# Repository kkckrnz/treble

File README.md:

# Treble
Treble keyboard is a 42 key, low profile choc v1, monoblock, moderate column staggered, wireless/wired mechanical keyboard powered by pro micro compatible MCU board. It is designed with [ergogen](https://github.com/ergogen/ergogen), the ergonomic keyboard generator.

The sandwich PCB design concept came from [Horizon keyboard](https://github.com/skarrmann/horizon). Bottom plate cutouts for through-hole pins makes it so that keyboard can be put on any surface, and the cover plate hides all the other internal components. Overall, this design makes the keyboard clean, low profile and look more finished without needing a dedicated case.

## Features
- Rectangular design for improved stability; easier to place on your lap or a laptop
- Low profile: total height is about 15mm tall
- Compact: overall size smaller than Apple Magic Keyboard
- Column staggered: mildly staggered so it's easy transition from row staggered keyboard yet it provides more comfortable typing experience
- 6 thumb keys: enough thumb keys for switching to different layers
- PCBs-for-case design
- Wireless/Wired depending on your preference

## Bill of Materials

| **Part**                             | **Quantity** | **Notes**                                           |
| ------------------------------------ | ------------ | --------------------------------------------------- |
| **Main PCB**                         | 1            | treble_vx.x.zip                                     |
| **Cover plate PCB**                  | 1            | treble_vx.x_cover_plate.zip                         |
| **Bottom plate PCB**                 | 1            | treble_vx.x_bottom_plate.zip                        |
| **MCU board**                        | 1            | Pro Micro compatible board                          |
| **Machine Sockets**                  | 2            | Mill-Max 310                                        |
| **Machine Socket Pins**              | 24           | Mill-Max 3320                                       |
| **Key switches**                     | 42           | Choc v1                                             |
| **Keycaps**                          | 42           | Choc v1 compatible                                  |
| **Diodes**                           | 42           | 1N4148 SOD-123                                      |
| **Reset switch**                     | 1            | EVQPU                                               |
| **Power switch**                     | 1            | MSK-12C02                                           |
| **JST connector (female)**           | 1            | S2B-PH-K-S                                          |
| **JST connector (male)**             | 1            |                                                     |
| **Battery**                          | 1            | 301230 110mAh 3.7V LiPo                             |
| **M2 6mm screws**                    | 12           |                                                     |
| **M2 nuts**                          | 4            |                                                     |
| **M2 8mm standoffs (female-female)** | 4            |                                                     |
| **Rubber feet**                      | 6            |                                                     |

- Male JST connector is only needed if the battery doesn't come with it
- You don't need Power switch, JST connector, and Battery if you build a wired keyboard

## Printable Treble
Download [Treble-A4.pdf](/docs/treble-A4.pdf) and print it (scale at 100%). Test the keyboard layout with your own hands.

## PCB order guide
1. Download gerber files from *Releases* on sidebar
2. Submit gerber files to PCB manufacturer
3. Select manufacturing options
4. Order

### JLCPCB manufacturing options
Most options are default. Changed options in *italic*:
- Base Material: FR-4
- Layers: 2
- Dimensions: (automatically filled in)
- PCB Qty: 5
- Product Type: Industrial/Consumer electronics
- Different Design: 1
- Delivery Format: Single PCB
- PCB Thickness: 1.6
- PCB Color: *Black*
- Silkscreen: White
- Surface Finish: *LeadFree HASL*
- Outer Copper Weight: 1 oz
- Via Covering: Tented
- Min via hole size/diameter: 0.3mm/(0.4/0.45mm)
- Board Outline Tolerance: ±0.2mm(Regular)
- Confirm Production file: No
- Mark on PCB: *Remove Mark*
- Electrical Test: Flying Probe Fully Test
- Gold Fingers: No
- Castellated Holes: No
- Edge Plating: No

I recommend **LeadFree HASL** option because you will be handling the keyboard directly without a case. Pick the PCB color of your choice. **Remove Mark** so you won't see random number printed on the PCB.

## Firmware
### ZMK
1. Setup GitHub Repo by following [ZMK documentation](https://zmk.dev/docs/user-setup#github-repo)
2. Setup User Config by following [ZMK documentation](https://zmk.dev/docs/user-setup#user-config-setup-script)	
3. Copy & Paste `/boards`, `/config`, and `build.yaml` from [zmk-config folder](/firmware/zmk-config) in this repo to zmk-config folder in your repo
4. Customise `treble.keymap` and `treble.conf` files in `/config` however you like it. Then push changes to your repo
```
git add .
git commit -m "commit message"
git push -u origin main
```
5. Install firmware by following [ZMK documentation](https://zmk.dev/docs/user-setup#installing-the-firmware)

- If you use MCU board other than nice!nano v2, then you will have to edit `build.yaml` file.
- [Precompiled firmware](/firmware/treble-nice_nano_v2-zmk.uf2.zip) is also available.
- There's [video guide](https://www.youtube.com/watch?v=O_urj-rF3bQ) by Joe Scotto if you would rather setup from scratch.

### Other Firmware
Since the keyboard is pro micro compatible it should be able to run QMK & KMK as well (not tested).

## Build guide
Follow [Build Guide](docs/treble_build_guide.md) to assemble the keyboard.

## Feedback
For any issues or questions please let me know.

If you have built and enjoyed the keyboard, consider supporting me.

Future development ideas:
- QMK & KMK firmware
- Hot swap switch support
- Low profile case
- MX version

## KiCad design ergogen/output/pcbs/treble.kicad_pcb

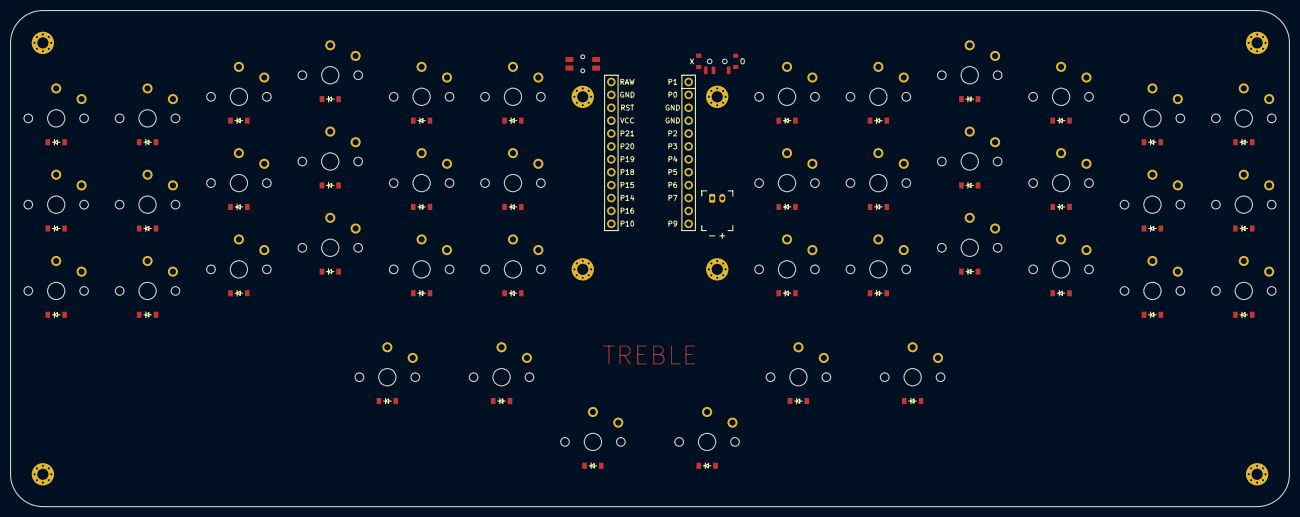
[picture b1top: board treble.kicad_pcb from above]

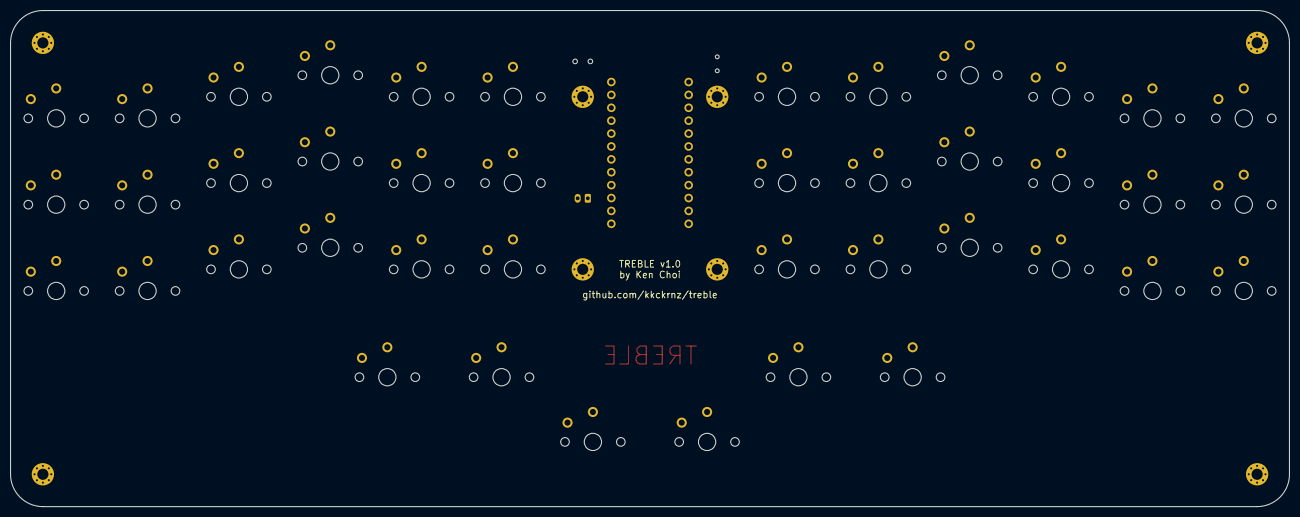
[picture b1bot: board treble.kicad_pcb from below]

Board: 2 copper layers, 252.0 x 97.8 mm, 141 parts (42 on the bottom side), 59 nets, no tracks yet.

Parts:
CJ1: CutoutMCU
CM1: CutoutMCU
CS1, CS2, CS3, CS4, CS5, CS6, CS7, CS8, CS9, CS10, CS11, CS12, CS13, CS14, CS15, CS16, CS17, CS18, CS19, CS20, CS21, CS22, CS23, CS24, CS25, CS26, CS27, CS28, CS29, CS30, CS31, CS32, CS33, CS34, CS35, CS36, CS37, CS38, CS39, CS40, CS41, CS42: CutoutSwitch
D1, D2, D3, D4, D5, D6, D7, D8, D9, D10, D11, D12, D13, D14, D15, D16, D17, D18, D19, D20, D21, D22, D23, D24, D25, D26, D27, D28, D29, D30, D31, D32, D33, D34, D35, D36, D37, D38, D39, D40, D41, D42: diode_tht_sod123
H1, H2, H3, H4, H5, H6, H7, H8: MountingHole_2.2mm_M2_Pad_Via
JST1: battery_connector_jst_ph_2
MCU1: mcu_nice_nano
PWR1: power_switch_smd_side
RA1: RuledArea
RST1: reset_switch_smd_side
S1, S2, S3, S4, S5, S6, S7, S8, S9, S10, S11, S12, S13, S14, S15, S16, S17, S18, S19, S20, S21, S22, S23, S24, S25, S26, S27, S28, S29, S30, S31, S32, S33, S34, S35, S36, S37, S38, S39, S40, S41, S42: switch_choc_v1_v2

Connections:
BAT_P: JST1.2, PWR1.1
GND: JST1.1, MCU1.3, MCU1.4, MCU1.23, RST1.1, RST1.3
P5: D24.1, D27.1, D30.1, D33.1, D36.1, D39.1, MCU1.8
P6: D23.1, D26.1, D29.1, D32.1, D35.1, D38.1, MCU1.9
P7: D22.1, D25.1, D28.1, D31.1, D34.1, D37.1, MCU1.10
P8: D19.1, D20.1, D21.1, D40.1, D41.1, D42.1, MCU1.11
P9: D1.1, D4.1, D7.1, D10.1, D13.1, D16.1, MCU1.12
P10: MCU1.13, S1.2, S2.2, S3.2, S37.2, S38.2, S39.2, S42.2
P14: MCU1.15, S7.2, S8.2, S9.2, S31.2, S32.2, S33.2, S40.2
P15: MCU1.16, S10.2, S11.2, S12.2, S19.2, S28.2, S29.2, S30.2
P16: MCU1.14, S4.2, S5.2, S6.2, S34.2, S35.2, S36.2, S41.2
P18: MCU1.17, S13.2, S14.2, S15.2, S20.2, S25.2, S26.2, S27.2
P19: MCU1.18, S16.2, S17.2, S18.2, S21.2, S22.2, S23.2, S24.2
P20: D2.1, D5.1, D8.1, D11.1, D14.1, D17.1, MCU1.19
P21: D3.1, D6.1, D9.1, D12.1, D15.1, D18.1, MCU1.20
RAW: MCU1.24, PWR1.2
RST: MCU1.22, RST1.2, RST1.4
home_thumb: D20.2, S20.1
index_bottom: D13.2, S13.1
index_home: D14.2, S14.1
index_top: D15.2, S15.1
inner_bottom: D16.2, S16.1
inner_home: D17.2, S17.1
inner_thumb: D19.2, S19.1
inner_top: D18.2, S18.1
middle_bottom: D10.2, S10.1
middle_home: D11.2, S11.1
middle_top: D12.2, S12.1
mirror_home_thumb: D41.2, S41.1
mirror_index_bottom: D34.2, S34.1
mirror_index_home: D35.2, S35.1
mirror_index_top: D36.2, S36.1
mirror_inner_bottom: D37.2, S37.1
mirror_inner_home: D38.2, S38.1
mirror_inner_thumb: D40.2, S40.1
mirror_inner_top: D39.2, S39.1
mirror_middle_bottom: D31.2, S31.1
mirror_middle_home: D32.2, S32.1
mirror_middle_top: D33.2, S33.1
mirror_outer_bottom: D22.2, S22.1
mirror_outer_home: D23.2, S23.1
mirror_outer_thumb: D42.2, S42.1
mirror_outer_top: D24.2, S24.1
mirror_pinky_bottom: D25.2, S25.1
mirror_pinky_home: D26.2, S26.1
mirror_pinky_top: D27.2, S27.1
mirror_ring_bottom: D28.2, S28.1
mirror_ring_home: D29.2, S29.1
mirror_ring_top: D30.2, S30.1
outer_bottom: D1.2, S1.1
outer_home: D2.2, S2.1
outer_thumb: D21.2, S21.1
outer_top: D3.2, S3.1
pinky_bottom: D4.2, S4.1
pinky_home: D5.2, S5.1
pinky_top: D6.2, S6.1
ring_bottom: D7.2, S7.1
ring_home: D8.2, S8.1
ring_top: D9.2, S9.1

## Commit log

2024-09-15 upload all files
2024-09-15 fix error in readme.md
2024-09-15 fix internal links in readme.md
2024-09-15 update readme.md with feedback
2024-09-15 fix shields.io
2024-09-15 add treble-A4.pdf
2024-09-16 upload smd images
2024-09-16 update readme & build guide
2024-09-16 fix image file format
2024-09-16 Rename treble_pcbs.JPG to treble_pcbs.jpg
    file format lower case
2024-09-16 remove empty space in readme
2024-09-16 added socket image
2024-09-16 optimise images
2024-09-26 update keyboard images
2024-09-26 fix image file name
2024-09-26 Rename treble_bottom.JPG to treble_bottom.jpg
2024-09-26 removed images
2024-09-26 Revert "Rename treble_bottom.JPG to treble_bottom.jpg"
    This reverts commit a80038cc5c39ff1c4682ac844adccfcf5cd78ed7.
2024-09-26 removed wrong image file
2024-09-26 added back images
2024-09-26 update build guide with images
2024-09-26 placeholder image removed
2024-09-27 fix kepmap comment, upload precompiled firmware
2024-09-27 update readme and build guide
2024-09-27 update image
2024-09-27 build guide jst note
2024-09-27 fix jst pin length
